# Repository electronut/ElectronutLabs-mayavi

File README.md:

# mayavi

A BLE OLED watch for Maya.

## Specifications

- Nordic nRF52832 BLE Raytac MDBT42v
- 0.96" OLED display
- ST Micro LIS2D12 accelerometer
- 2 x [Side mounted buttons][1]
- 140 mAh LiPo battery
- Buzzer

[1]: https://www.sunrom.com/p/tactile-switch-smd-3x6mm-side-press

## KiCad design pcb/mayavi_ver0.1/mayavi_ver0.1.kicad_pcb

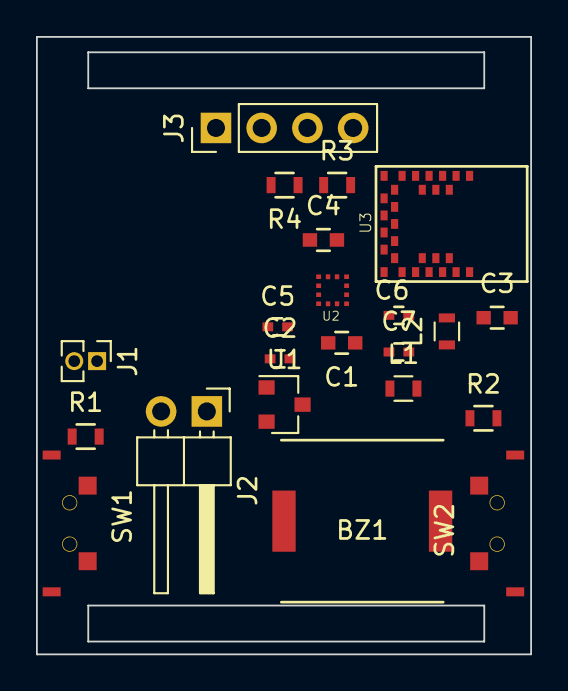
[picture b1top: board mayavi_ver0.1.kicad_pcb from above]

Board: 2 copper layers, 27.5 x 34.3 mm, 23 parts (1 on the bottom side), 16 nets, no tracks yet.

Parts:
BZ1: Buzzer; PKMCS0909E4000-R1
C1: 10uF; C_0603
C2, C7: 1uF; C_0402
C3, C4: 0.1uF; C_0603
C5, C6: 10uF; C_0402
J1: 3.7V LiPo; Pin_Header_Straight_1x02_Pitch1.27mm
J2: Charging Conn; Pin_Header_Angled_1x02_Pitch2.54mm
J3: OLED Connector; Pin_Header_Straight_1x04_Pitch2.54mm
J4: SWD header; SWD_1.27
L1, L2: 10uH; L_0603
R1, R2, R3, R4: 10K; R_0603
SW1, SW2: SW_Push; SW5052
U1: MCP1702; SOT-23
U2: LIS2DH12; LIS2DH12-LGA12_2X2MM
U3: MDBT42V

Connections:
BTN1: R1.2, U3.14
BTN2: R2.2, U3.13
BuzN: BZ1.2, U3.12
BuzP: BZ1.1, U3.11
GND: C1.2, C2.2, C3.2, C4.2, C5.2, C6.2, C7.2, J1.2, J2.2, J3.4, J4.4, U1.1, U2.5, U2.6, U2.7, U2.8, U3.1, U3.10, U3.18, U3.29
INT1: U2.12, U3.26
INT2: U2.11, U3.25
unnamed: C7.1, L2.2, U3.21
unnamed: L1.1, U3.22
unnamed: L1.2, L2.1
SCL: J3.3, R4.2, U2.1, U3.28
SDA: J3.2, R3.2, U2.4, U3.27
SWDCLK: J4.2, U3.2
SWDIO: J4.1, U3.4
VBAT: C2.1, J1.1, J2.1, J3.1, U1.3
VDD: C1.1, C3.1, C4.1, C5.1, C6.1, J4.3, R1.1, R2.1, R3.1, R4.1, U1.2, U2.2, U2.3, U2.9, U2.10, U3.20

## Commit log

2018-06-09 added code
2018-06-10 added accel
2018-06-11 SDK 15 works with rtc and display
2018-06-12 added NUS
2018-06-14 added schematic
2018-06-15 updated schematic
2018-06-18 code reorg
2018-06-20 using app_timer
2018-06-21 added pwm and melody
2018-06-21 added state diagram
2018-07-01 added time format
2018-07-01 setting time over ble
2018-07-01 updated docw
2018-07-02 set time
2018-07-04 music playing
2018-07-05 Added drawing code
2018-07-05 updated pcb
